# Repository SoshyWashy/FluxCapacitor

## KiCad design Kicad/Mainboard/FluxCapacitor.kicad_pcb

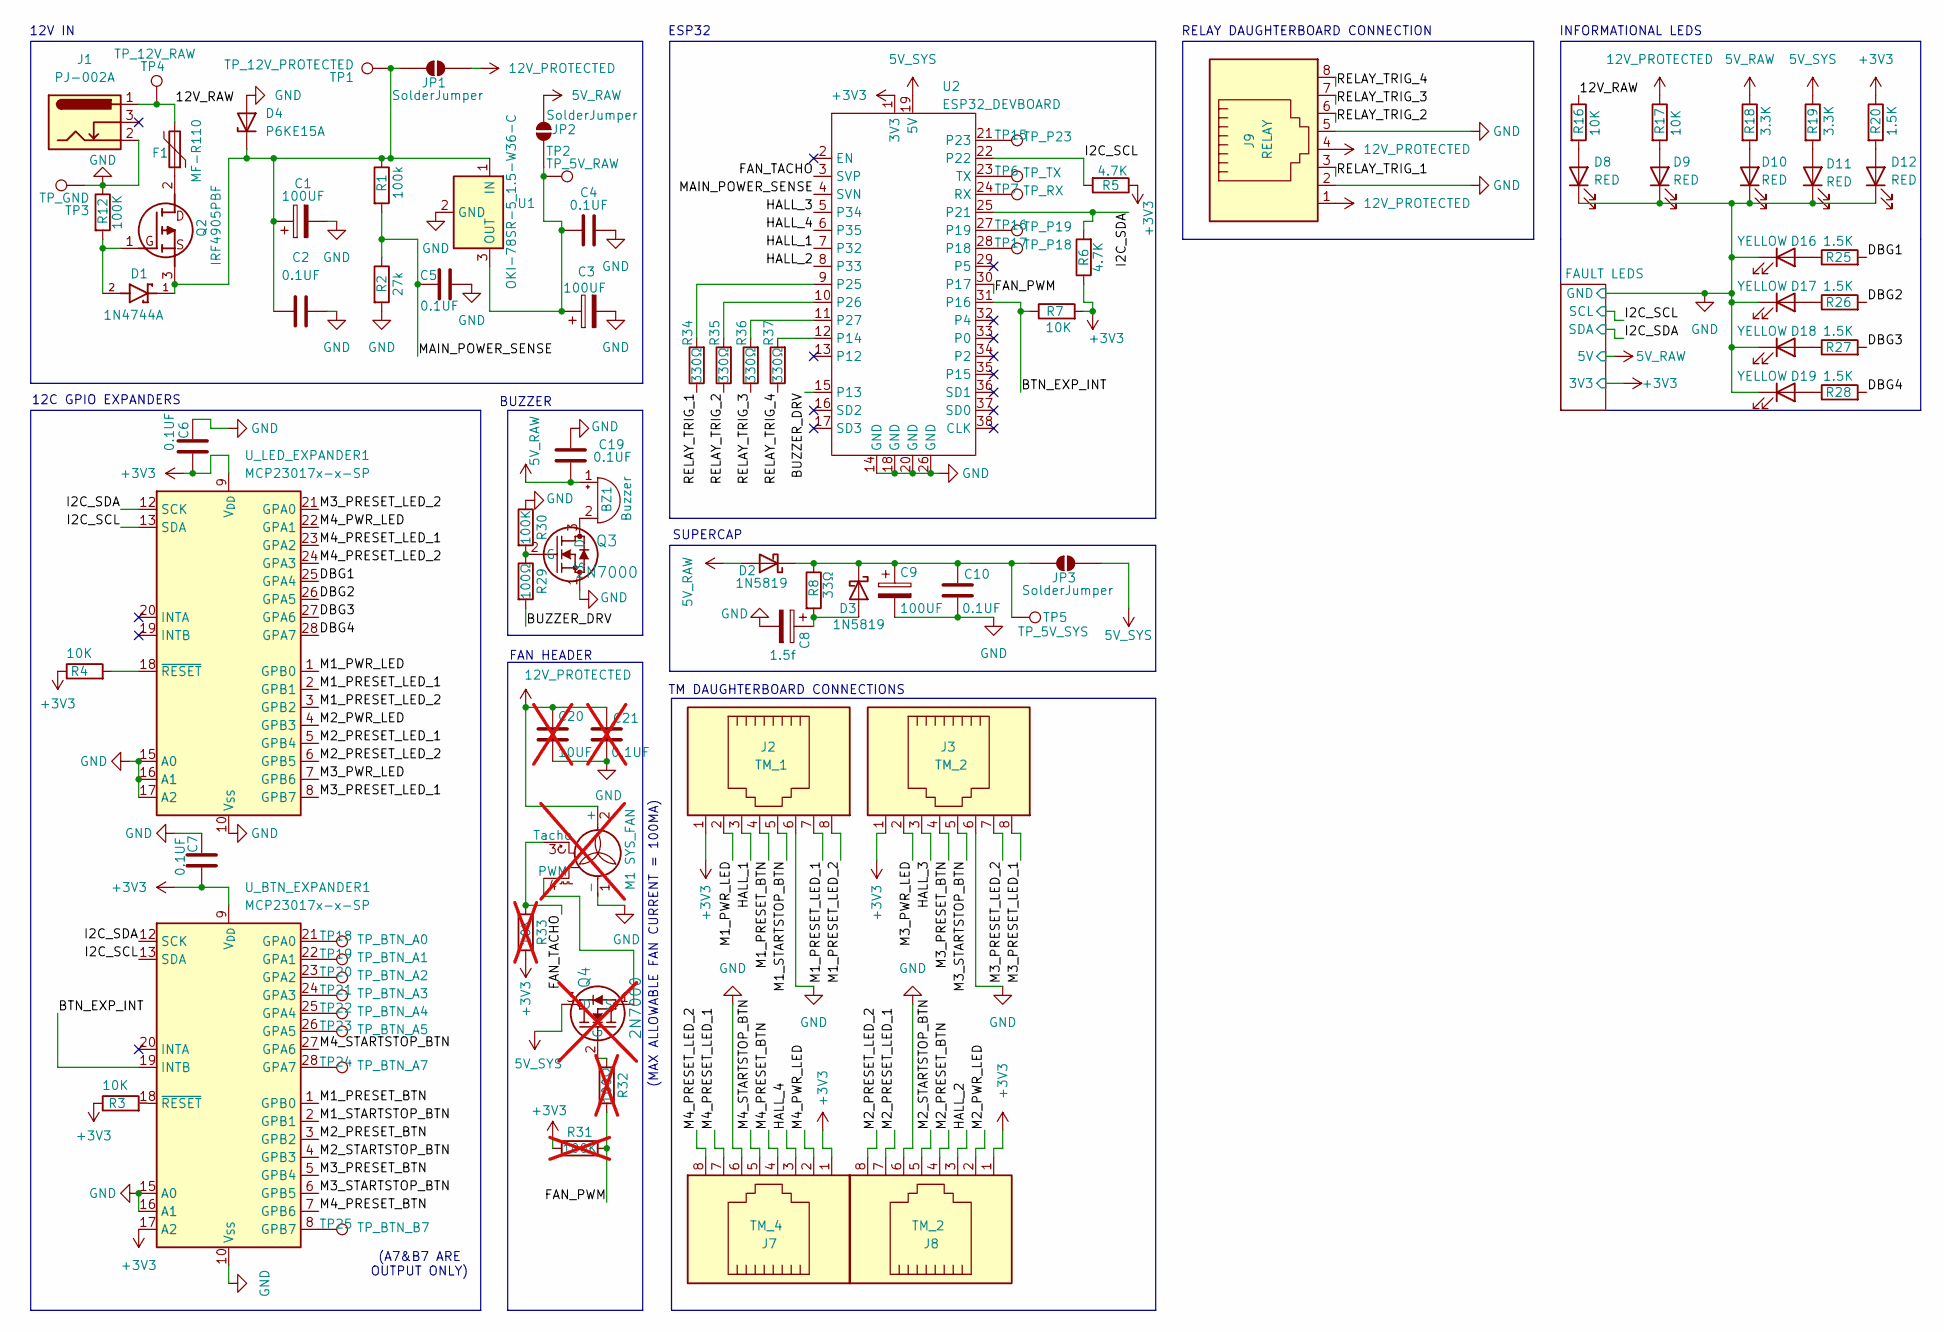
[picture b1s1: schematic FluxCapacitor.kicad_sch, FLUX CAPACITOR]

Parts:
BZ1: Buzzer; PT2040PQ
C1, C3, C9: 100UF; 25YXJ100M5X11
C2, C4, C5, C6, C7, C10, C19: 0.1UF; CC0805KRX7R9BB104
C8: 1.5f; PHV-5R4V155-R
C20: 10UF; GMC21X7R106K25NT; not fitted
C21: 0.1UF; CC0805KRX7R9BB104; not fitted
D1: 1N4744A; PARTREV 10
D2, D3: 1N5819; D_DO-41_SOD81_P10.16mm_Horizontal
D4: P6KE15A
D8, D9, D10, D11, D12: RED; LED_0805_2012Metric_Pad1.15x1.40mm_HandSolder
D16, D17, D18, D19: YELLOW; LED_0805_2012Metric_Pad1.15x1.40mm_HandSolder
F1: MF-R110
J1: PJ-002A
J2: TM_1; SS-6488-NF-50
J3, J8: TM_2; SS-6488-NF-50
J7: TM_4; SS-6488-NF-50
J9: RELAY; SS-6488-NF-50
JP1, JP2, JP3: SolderJumper; SolderJumper-2_P1.3mm_Open_Pad1.0x1.5mm
M1: SYS_FAN; FanPinHeader_1x04_P2.54mm_Vertical; not fitted
Q2: IRF4905PBF; Mouser Part Number 942-IRF4905PBF
Q3: 2N7000
Q4: 2N7000; not fitted
R1: 100k; R_0805_2012Metric_Pad1.20x1.40mm_HandSolder
R2: 27k; R_0805_2012Metric_Pad1.20x1.40mm_HandSolder
R3, R4, R7, R16, R17: 10K; R_0805_2012Metric_Pad1.20x1.40mm_HandSolder
R5, R6: 4.7K; R_0805_2012Metric_Pad1.20x1.40mm_HandSolder
R8: 33Ω; R_0805_2012Metric_Pad1.20x1.40mm_HandSolder
R12, R30: 100K; R_0805_2012Metric_Pad1.20x1.40mm_HandSolder
R18, R19: 3.3K; R_0805_2012Metric_Pad1.20x1.40mm_HandSolder
R20, R25, R26, R27, R28: 1.5K; R_0805_2012Metric_Pad1.20x1.40mm_HandSolder
R29: 100Ω; R_0805_2012Metric_Pad1.20x1.40mm_HandSolder
R31: 100K; R_0805_2012Metric_Pad1.20x1.40mm_HandSolder; not fitted
R32: 100Ω; R_0805_2012Metric_Pad1.20x1.40mm_HandSolder; not fitted
R33: 10K; R_0805_2012Metric_Pad1.20x1.40mm_HandSolder; not fitted
R34, R35, R36, R37: 330Ω; R_0805_2012Metric_Pad1.20x1.40mm_HandSolder
TP1: TP_12V_PROTECTED; TestPoint_Pad_D2.0mm
TP2: TP_5V_RAW; TestPoint_Pad_D2.0mm
TP3: TP_GND; TestPoint_Pad_D2.0mm
TP4: TP_12V_RAW; TestPoint_Pad_D2.0mm
TP5: TP_5V_SYS; TestPoint_Pad_D2.0mm
TP6: TP_TX; TestPoint_Pad_D1.5mm
TP7: TP_RX; TestPoint_Pad_D1.5mm
TP15: TP_P23; TestPoint_Pad_D1.5mm
TP16: TP_P19; TestPoint_Pad_D1.5mm
TP17: TP_P18; TestPoint_Pad_D1.5mm
TP18: TP_BTN_A0; TestPoint_Pad_D1.5mm
TP19: TP_BTN_A1; TestPoint_Pad_D1.5mm
TP20: TP_BTN_A2; TestPoint_Pad_D1.5mm
TP21: TP_BTN_A3; TestPoint_Pad_D1.5mm
TP22: TP_BTN_A4; TestPoint_Pad_D1.5mm
TP23: TP_BTN_A5; TestPoint_Pad_D1.5mm
TP24: TP_BTN_A7; TestPoint_Pad_D1.5mm
TP25: TP_BTN_B7; TestPoint_Pad_D1.5mm
U1: OKI-78SR-5_1.5-W36-C; Converter_DCDC_Murata_OKI-78SR_Vertical
U2: ESP32_DEVBOARD; ESP32 DEVBOARD
U_BTN_EXPANDER1: MCP23017x-x-SP; DIP-28_W7.62mm
U_LED_EXPANDER1: MCP23017x-x-SP; DIP-28_W7.62mm

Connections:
5V_RAW: BZ1.1 (+), C19.2, D2.2 (A), JP2.2 (B), R18.1; also elsewhere on the board
5V_SYS: JP3.2 (B), Q4.3 (D), R19.1, U2.19 (5V)
12V_PROTECTED: C20.1, C21.1, J9.1, J9.4, JP1.2 (B), M1.2 (+), R17.1
+3V3: C6.2, C7.2, J2.1, J3.1, J7.1, J8.1, R3.1, R4.1, R5.1, R6.1, R7.2, R20.1, R31.1, R33.2, U2.1 (3V3), U_BTN_EXPANDER1.9 (V_{DD}), U_BTN_EXPANDER1.17 (A2), U_LED_EXPANDER1.9 (V_{DD}); also elsewhere on the board
/12V_RAW: F1.2, J1.1, R16.1, TP4.1 (1_1)
/BTN_EXP_INT: R7.1, U2.31 (P16), U_BTN_EXPANDER1.19 (INTB)
/BUZZER_DRV: R29.2, U2.15 (P13)
/DBG1: R25.2, U_LED_EXPANDER1.25 (GPA4)
/DBG2: R26.2, U_LED_EXPANDER1.26 (GPA5)
/DBG3: R27.2, U_LED_EXPANDER1.27 (GPA6)
/DBG4: R28.2, U_LED_EXPANDER1.28 (GPA7)
/FAN_PWM: R31.2, R32.2, U2.30 (P17)
/FAN_TACHO: M1.3 (Tacho), R33.1, U2.3 (SVP)
/HALL_1: J2.3, U2.7 (P32)
/HALL_2: J8.3, U2.8 (P33)
/HALL_3: J3.3, U2.5 (P34)
/HALL_4: J7.3, U2.6 (P35)
/I2C_SCL: R5.2, U2.22, U_BTN_EXPANDER1.13 (SDA), U_LED_EXPANDER1.13 (SDA); also elsewhere on the board
/I2C_SDA: R6.2, U2.25 (P21), U_BTN_EXPANDER1.12 (SCK), U_LED_EXPANDER1.12 (SCK); also elsewhere on the board
/M1_PRESET_BTN: J2.4, U_BTN_EXPANDER1.1 (GPB0)
/M1_PRESET_LED_1: J2.7, U_LED_EXPANDER1.2 (GPB1)
/M1_PRESET_LED_2: J2.8, U_LED_EXPANDER1.3 (GPB2)
/M1_PWR_LED: J2.2, U_LED_EXPANDER1.1 (GPB0)
/M1_STARTSTOP_BTN: J2.5, U_BTN_EXPANDER1.2 (GPB1)
/M2_PRESET_BTN: J8.4, U_BTN_EXPANDER1.3 (GPB2)
/M2_PRESET_LED_1: J8.7, U_LED_EXPANDER1.5 (GPB4)
/M2_PRESET_LED_2: J8.8, U_LED_EXPANDER1.6 (GPB5)
/M2_PWR_LED: J8.2, U_LED_EXPANDER1.4 (GPB3)
/M2_STARTSTOP_BTN: J8.5, U_BTN_EXPANDER1.4 (GPB3)
/M3_PRESET_BTN: J3.4, U_BTN_EXPANDER1.5 (GPB4)
/M3_PRESET_LED_1: J3.8, U_LED_EXPANDER1.8 (GPB7)
/M3_PRESET_LED_2: J3.7, U_LED_EXPANDER1.21 (GPA0)
/M3_PWR_LED: J3.2, U_LED_EXPANDER1.7 (GPB6)
/M3_STARTSTOP_BTN: J3.5, U_BTN_EXPANDER1.6 (GPB5)
/M4_PRESET_BTN: J7.4, U_BTN_EXPANDER1.7 (GPB6)
/M4_PRESET_LED_1: J7.7, U_LED_EXPANDER1.23 (GPA2)
/M4_PRESET_LED_2: J7.8, U_LED_EXPANDER1.24 (GPA3)
/M4_PWR_LED: J7.2, U_LED_EXPANDER1.22 (GPA1)
/M4_STARTSTOP_BTN: J7.5, U_BTN_EXPANDER1.27 (GPA6)
/MAIN_POWER_SENSE: C5.1, R1.2, R2.1, U2.4 (SVN)
/RELAY_TRIG_1: J9.3, R34.1
/RELAY_TRIG_2: J9.6, R35.1
/RELAY_TRIG_3: J9.7, R36.1
/RELAY_TRIG_4: J9.8, R37.1
GND: C1.2, C2.2, C3.2, C4.2, C5.2, C6.1, C7.1, C8.2, C9.2, C10.2, C19.1, C20.2, C21.2, D4.2 (A), D8.1 (K), D9.1 (K), D10.1 (K), D11.1 (K), D12.1 (K), D16.1 (K), D17.1 (K), D18.1 (K), D19.1 (K), J1.2, J2.6, J3.6, J7.6, J8.6, J9.2, J9.5, M1.1 (-), Q3.1 (S), R2.2, R12.1, R30.1, TP3.1 (1_1), U1.2 (GND), U2.14 (GND), U2.18 (GND), U2.20 (GND), U2.26 (GND), U_BTN_EXPANDER1.10 (V_{SS}), U_BTN_EXPANDER1.15 (A0), U_BTN_EXPANDER1.16 (A1), U_LED_EXPANDER1.10 (V_{SS}), U_LED_EXPANDER1.15 (A0), U_LED_EXPANDER1.16 (A1), U_LED_EXPANDER1.17 (A2); also elsewhere on the board
unnamed: BZ1.2 (-), Q3.3 (D)
unnamed: C9.1, C10.1, D2.1 (K), D3.1 (K), JP3.1 (A), R8.1, TP5.1 (1_1)
unnamed: C8.1, D3.2 (A), R8.2
unnamed: C1.1, C2.1, D1.1, D4.1 (K), JP1.1 (A), Q2.3 (S), R1.1, TP1.1 (1_1), U1.1 (IN)
unnamed: D8.2 (A), R16.2
unnamed: D9.2 (A), R17.2
unnamed: D10.2 (A), R18.2
unnamed: D11.2 (A), R19.2
unnamed: D12.2 (A), R20.2
unnamed: D16.2 (A), R25.1
unnamed: D17.2 (A), R26.1
unnamed: D18.2 (A), R27.1
unnamed: D19.2 (A), R28.1
unnamed: C3.1, C4.1, JP2.1 (A), TP2.1 (1_1), U1.3 (OUT)
unnamed: M1.4 (PWM), Q4.1 (S)
unnamed: F1.1, Q2.2 (D)
unnamed: D1.2, Q2.1 (G), R12.2
unnamed: Q3.2 (G), R29.1, R30.2
unnamed: Q4.2 (G), R32.1
unnamed: R37.2, U2.12 (P14)
unnamed: TP17.1 (1_1), U2.28 (P18)
unnamed: TP16.1 (1_1), U2.27 (P19)
unnamed: TP15.1 (1_1), U2.21 (P23)
unnamed: R34.2, U2.9 (P25)
unnamed: R35.2, U2.10 (P26)
unnamed: R36.2, U2.11 (P27)
unnamed: TP7.1 (1_1), U2.24 (RX)
unnamed: TP6.1 (1_1), U2.23 (TX)
unnamed: TP18.1 (1_1), U_BTN_EXPANDER1.21 (GPA0)
unnamed: TP19.1 (1_1), U_BTN_EXPANDER1.22 (GPA1)
unnamed: TP20.1 (1_1), U_BTN_EXPANDER1.23 (GPA2)
unnamed: TP21.1 (1_1), U_BTN_EXPANDER1.24 (GPA3)
unnamed: TP22.1 (1_1), U_BTN_EXPANDER1.25 (GPA4)
unnamed: TP23.1 (1_1), U_BTN_EXPANDER1.26 (GPA5)
unnamed: TP24.1 (1_1), U_BTN_EXPANDER1.28 (GPA7)
unnamed: TP25.1 (1_1), U_BTN_EXPANDER1.8 (GPB7)
unnamed: R3.2, U_BTN_EXPANDER1.18 (~RESET)
unnamed: R4.2, U_LED_EXPANDER1.18 (~RESET)

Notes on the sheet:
INFORMATIONAL LEDS
RELAY DAUGHTERBOARD CONNECTION
SUPERCAP
BUZZER
12V IN
TM DAUGHTERBOARD CONNECTIONS
12C GPIO EXPANDERS
(MAX ALLOWABLE FAN CURRENT = 100MA)
ESP32
FAN HEADER
(A7&B7 ARE OUTPUT ONLY)

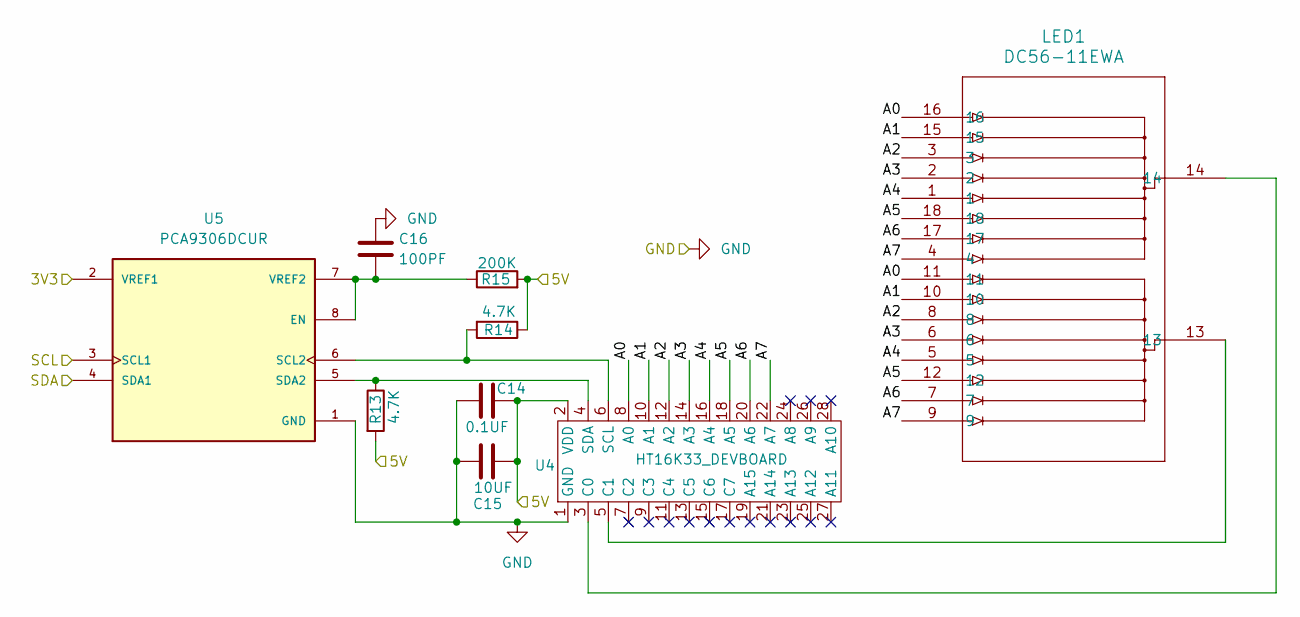
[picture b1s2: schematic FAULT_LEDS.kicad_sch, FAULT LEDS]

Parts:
C14: 0.1UF; CC0805KRX7R9BB104
C15: 10UF; GMC21X7R106K25NT
C16: 100PF; C0805C101J5GACTU
LED1: DC56-11EWA
R13, R14: 4.7K; R_0805_2012Metric_Pad1.20x1.40mm_HandSolder
R15: 200K; R_0805_2012Metric_Pad1.20x1.40mm_HandSolder
U4: HT16K33_DEVBOARD; HT16K33 DEVBOARD
U5: PCA9306DCUR; PARTREV M

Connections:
5V_RAW: C14.2, C15.2, R13.2, R14.1, R15.2, U4.2 (VDD); also elsewhere on the board
+3V3: U5.2 (VREF1); also elsewhere on the board
/FAULT LEDS/A0: LED1.11, LED1.16, U4.8 (A0)
/FAULT LEDS/A1: LED1.10, LED1.15, U4.10 (A1)
/FAULT LEDS/A2: LED1.3, LED1.8, U4.12 (A2)
/FAULT LEDS/A3: LED1.2, LED1.6, U4.14 (A3)
/FAULT LEDS/A4: LED1.1, LED1.5, U4.16 (A4)
/FAULT LEDS/A5: LED1.12, LED1.18, U4.18 (A5)
/FAULT LEDS/A6: LED1.7, LED1.17, U4.20 (A6)
/FAULT LEDS/A7: LED1.4, LED1.9, U4.22 (A7)
/I2C_SCL: U5.3 (SCL1); also elsewhere on the board
/I2C_SDA: U5.4 (SDA1); also elsewhere on the board
GND: C14.1, C15.1, C16.1, U4.1 (GND), U5.1 (GND); also elsewhere on the board
unnamed: LED1.14, U4.3 (C0)
unnamed: LED1.13, U4.5 (C1)
unnamed: R14.2, U4.6 (SCL), U5.6 (SCL2)
unnamed: R13.1, U4.4 (SDA), U5.5 (SDA2)
unnamed: C16.2, R15.1, U5.7 (VREF2), U5.8 (EN)

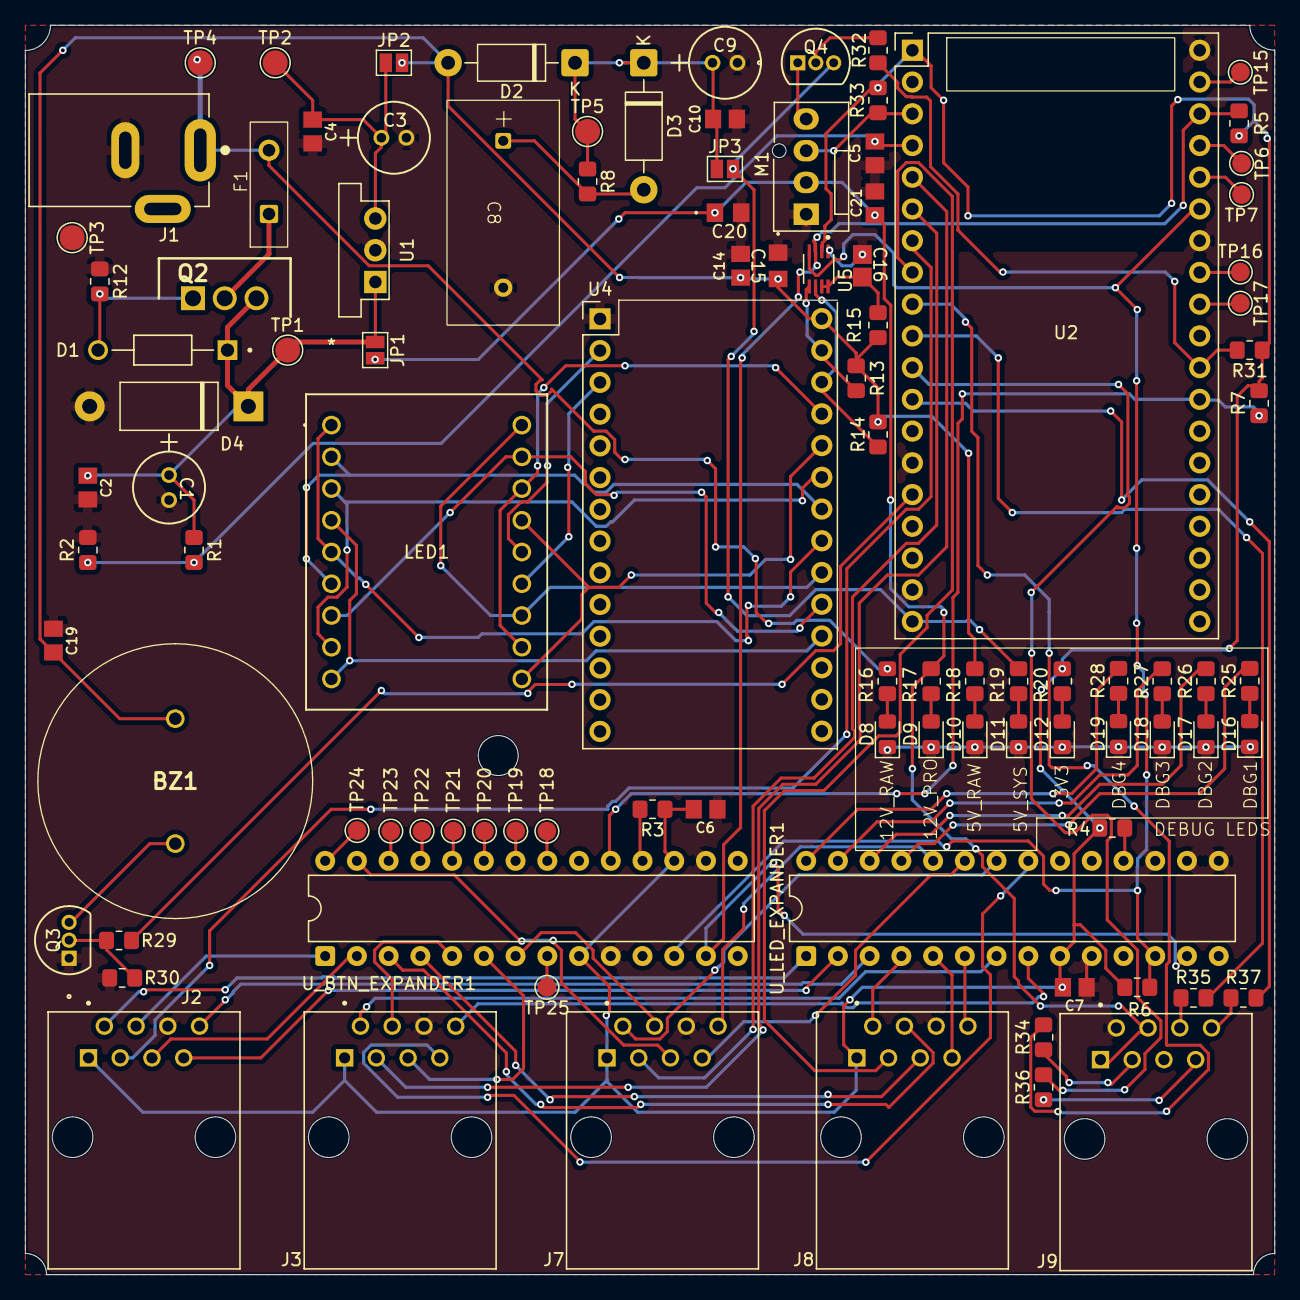
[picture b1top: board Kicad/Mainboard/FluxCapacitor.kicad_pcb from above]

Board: 2 copper layers, 100.0 x 100.0 mm, 99 parts (0 on the bottom side), 96 nets.

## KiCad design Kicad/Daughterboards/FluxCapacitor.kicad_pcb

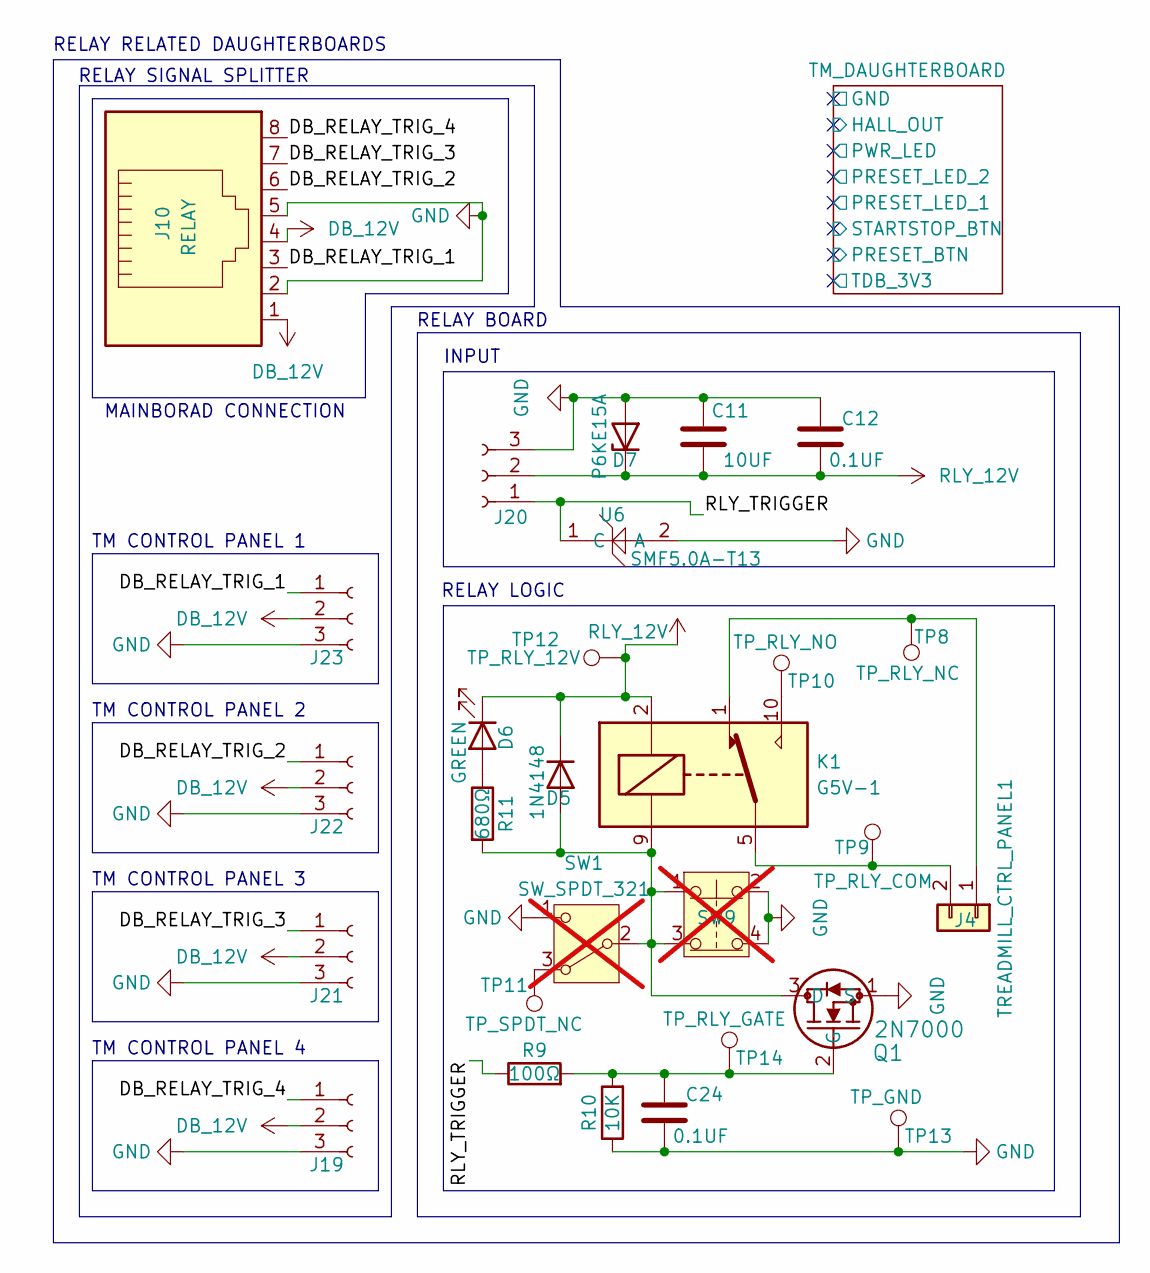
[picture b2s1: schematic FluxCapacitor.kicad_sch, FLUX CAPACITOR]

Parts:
C11: 10UF; GMC21X7R106K25NT
C12, C24: 0.1UF; CC0805KRX7R9BB104
D5: 1N4148
D6: GREEN; LED_0805_2012Metric_Pad1.15x1.40mm_HandSolder
D7: P6KE15A; Nexperia_DSN1608-2_1.6x0.8mm
J4: TREADMILL_CTRL_PANEL1; PinHeader_1x02_P2.54mm_Vertical
J10: RELAY; SS-6488-NF-50
J19, J20, J21, J22, J23: JST_PH_01x03_Socket; JST_PH_B3B-PH-K_1x03_P2.00mm_Vertical
K1: G5V-1; Relay_SPDT_Omron_G5V-1
Q1: 2N7000
R9: 100Ω; R_0805_2012Metric_Pad1.20x1.40mm_HandSolder
R10: 10K; R_0805_2012Metric_Pad1.20x1.40mm_HandSolder
R11: 680Ω; R_0805_2012Metric_Pad1.20x1.40mm_HandSolder
SW1: SW_SPDT_321; TM SPDT switch; not fitted
SW9: SW_Push_Open_Dual; D6R60F1LFS; not fitted
TP8: TP_RLY_NC; TestPoint_Pad_D2.0mm
TP9: TP_RLY_COM; TestPoint_Pad_D2.0mm
TP10: TP_RLY_NO; TestPoint_Pad_D2.0mm
TP11: TP_SPDT_NC; TestPoint_Pad_D2.0mm
TP12: TP_RLY_12V; TestPoint_Pad_D2.0mm
TP13: TP_GND; TestPoint_Pad_D2.0mm
TP14: TP_RLY_GATE; TestPoint_Pad_D2.0mm
U6: SMF5.0A-T13

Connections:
/DB_RELAY_TRIG_1: J10.3, J23.1
/DB_RELAY_TRIG_2: J10.6, J22.1
/DB_RELAY_TRIG_3: J10.7, J21.1
/DB_RELAY_TRIG_4: J10.8, J19.1
/RLY_TRIGGER: J20.1, R9.1, U6.1 (C)
DB_12V: J10.1, J10.4, J19.2, J21.2, J22.2, J23.2
GND: C11.2, C12.2, C24.1, D7.2 (A), J10.2, J10.5, J19.3, J20.3, J21.3, J22.3, J23.3, Q1.1 (S), R10.1, SW1.1 (C), SW9.2, SW9.4, TP13.1 (1_1), U6.2 (A); also elsewhere on the board
unnamed: D5.2 (A), K1.9, Q1.3 (D), R11.2, SW1.2 (B), SW9.1, SW9.3
unnamed: D6.2 (A), R11.1
unnamed: J4.1, K1.1, TP8.1 (1_1)
unnamed: J4.2, K1.5, K1.6, TP9.1 (1_1)
unnamed: K1.10, TP10.1 (1_1)
unnamed: C24.2, Q1.2 (G), R9.2, R10.2, TP14.1 (1_1)
unnamed: SW1.3 (A), TP11.1 (1_1)
RLY_12V: C11.1, C12.1, D5.1 (K), D6.1 (K), D7.1 (K), J20.2, K1.2, TP12.1 (1_1)

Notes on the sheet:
RELAY LOGIC
TM CONTROL PANEL 3
RELAY BOARD
TM CONTROL PANEL 4
MAINBORAD CONNECTION
INPUT
TM CONTROL PANEL 2
RELAY SIGNAL SPLITTER
TM CONTROL PANEL 1
RELAY RELATED DAUGHTERBOARDS

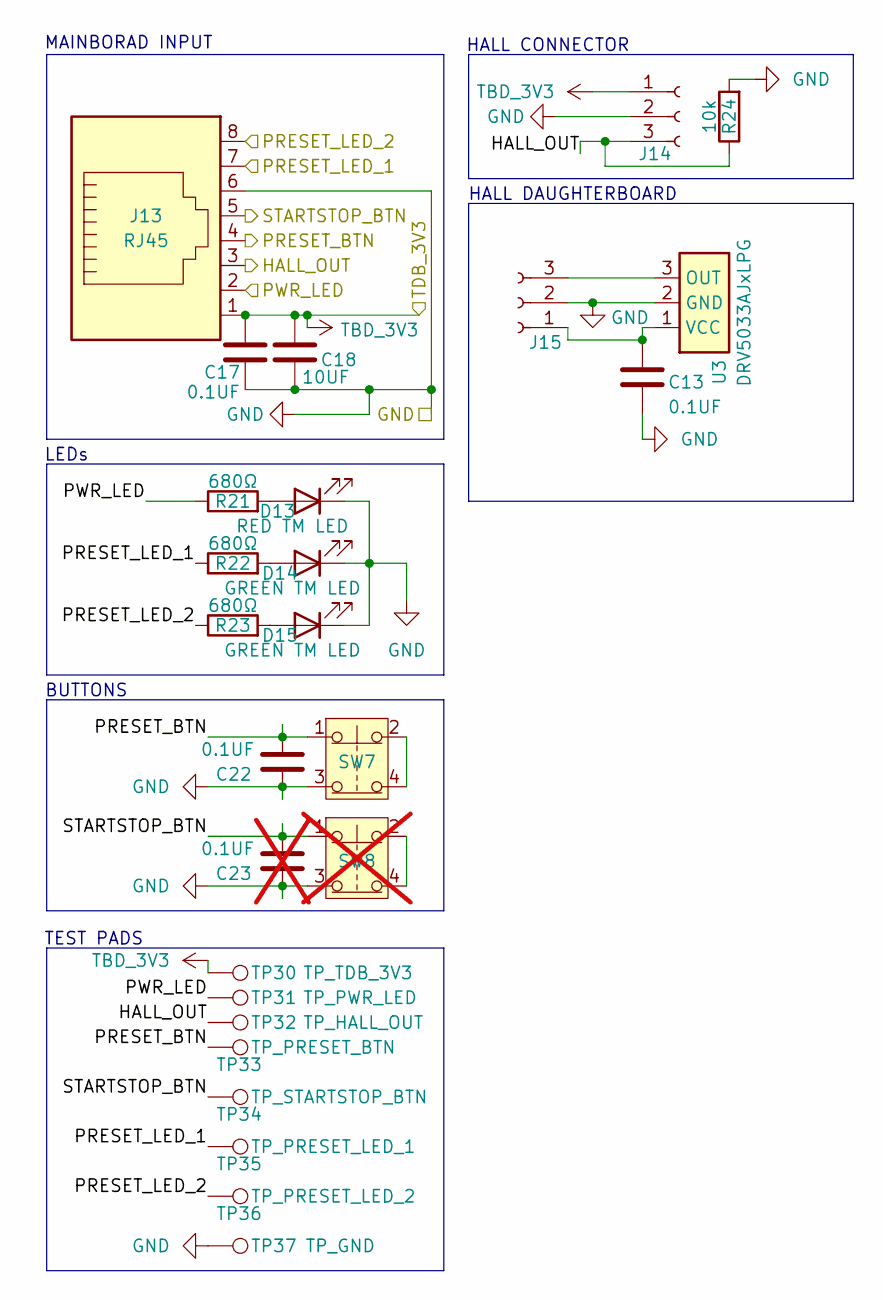
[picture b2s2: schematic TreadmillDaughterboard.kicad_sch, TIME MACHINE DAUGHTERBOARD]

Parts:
C13, C17, C22: 0.1UF; CC0805KRX7R9BB104
C18: 10UF; GMC21X7R106K25NT
C23: 0.1UF; CC0805KRX7R9BB104; not fitted
D13: RED TM LED; LED_D5.0mm
D14, D15: GREEN TM LED; LED_D5.0mm
J13: RJ45; SS-6488-NF-50
J14, J15: Conn_01x03_Socket; JST_PH_B3B-PH-K_1x03_P2.00mm_Vertical
R21, R22, R23: 680Ω; R_0805_2012Metric_Pad1.20x1.40mm_HandSolder
R24: 10k; R_0805_2012Metric_Pad1.20x1.40mm_HandSolder
SW7: SW_Push_Open_Dual; D6R60F1LFS
SW8: SW_Push_Open_Dual; D6R60F1LFS; not fitted
TP30: TP_TDB_3V3; TestPoint_Pad_D2.0mm
TP31: TP_PWR_LED; TestPoint_Pad_D2.0mm
TP32: TP_HALL_OUT; TestPoint_Pad_D2.0mm
TP33: TP_PRESET_BTN; TestPoint_Pad_D2.0mm
TP34: TP_STARTSTOP_BTN; TestPoint_Pad_D2.0mm
TP35: TP_PRESET_LED_1; TestPoint_Pad_D2.0mm
TP36: TP_PRESET_LED_2; TestPoint_Pad_D2.0mm
TP37: TP_GND; TestPoint_Pad_D2.0mm
U3: DRV5033AJxLPG; TO-92_Inline

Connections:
/TM_DAUGHTERBOARD/HALL_OUT: J13.3, J14.3, R24.1, TP32.1 (1_1)
/TM_DAUGHTERBOARD/PRESET_BTN: C22.2, J13.4, SW7.1, TP33.1 (1_1)
/TM_DAUGHTERBOARD/PRESET_LED_1: J13.7, R22.1, TP35.1 (1_1)
/TM_DAUGHTERBOARD/PRESET_LED_2: J13.8, R23.1, TP36.1 (1_1)
/TM_DAUGHTERBOARD/PWR_LED: J13.2, R21.1, TP31.1 (1_1)
/TM_DAUGHTERBOARD/STARTSTOP_BTN: C23.2, J13.5, SW8.1, TP34.1 (1_1)
GND: C13.2, C17.2, C18.2, C22.1, C23.1, D13.1 (K), D14.1 (K), D15.1 (K), J13.6, J14.2, J15.2, R24.2, SW7.3, SW8.3, TP37.1 (1_1), U3.2 (GND); also elsewhere on the board
unnamed: D13.2 (A), R21.2
unnamed: D14.2 (A), R22.2
unnamed: D15.2 (A), R23.2
unnamed: C13.1, J15.1, U3.1 (VCC)
unnamed: J15.3, U3.3 (OUT)
unnamed: SW7.2, SW7.4
unnamed: SW8.2, SW8.4
TBD_3V3: C17.1, C18.1, J13.1, J14.1, TP30.1 (1_1)

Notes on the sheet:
BUTTONS
HALL DAUGHTERBOARD
TEST PADS
MAINBORAD INPUT
HALL CONNECTOR
LEDs

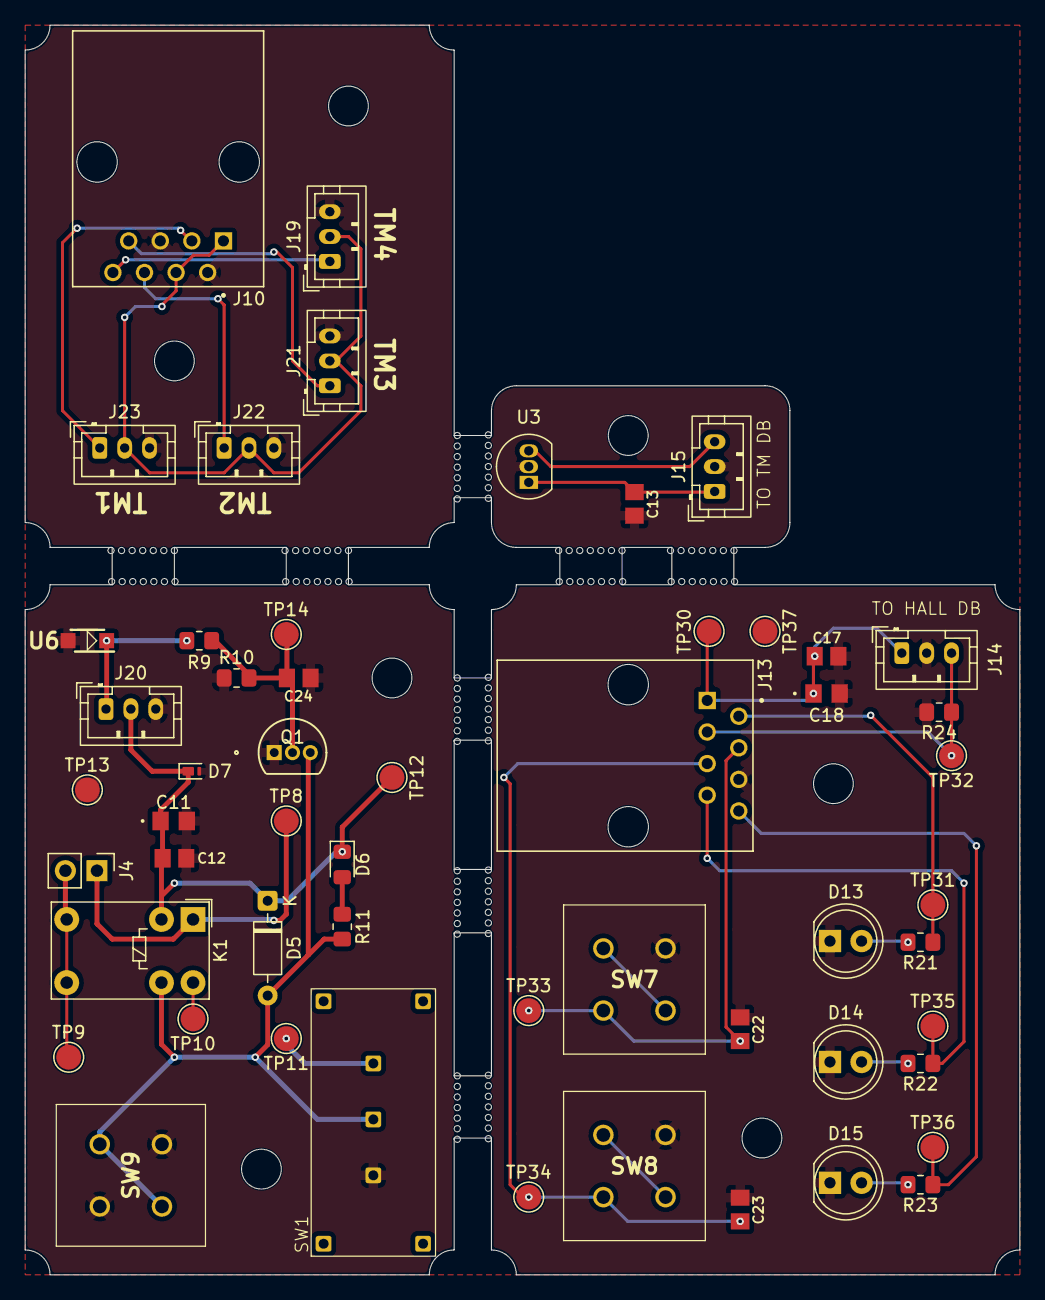
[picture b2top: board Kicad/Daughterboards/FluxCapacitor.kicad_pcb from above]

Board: 2 copper layers, 80.0 x 100.5 mm, 54 parts (0 on the bottom side), 29 nets.
